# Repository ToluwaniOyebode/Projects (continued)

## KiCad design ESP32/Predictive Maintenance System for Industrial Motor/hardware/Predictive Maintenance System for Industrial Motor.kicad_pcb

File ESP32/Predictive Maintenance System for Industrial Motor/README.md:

# Predictive Maintenance System for Industrial Motor
Generated using KiCad Industrial Setup Script

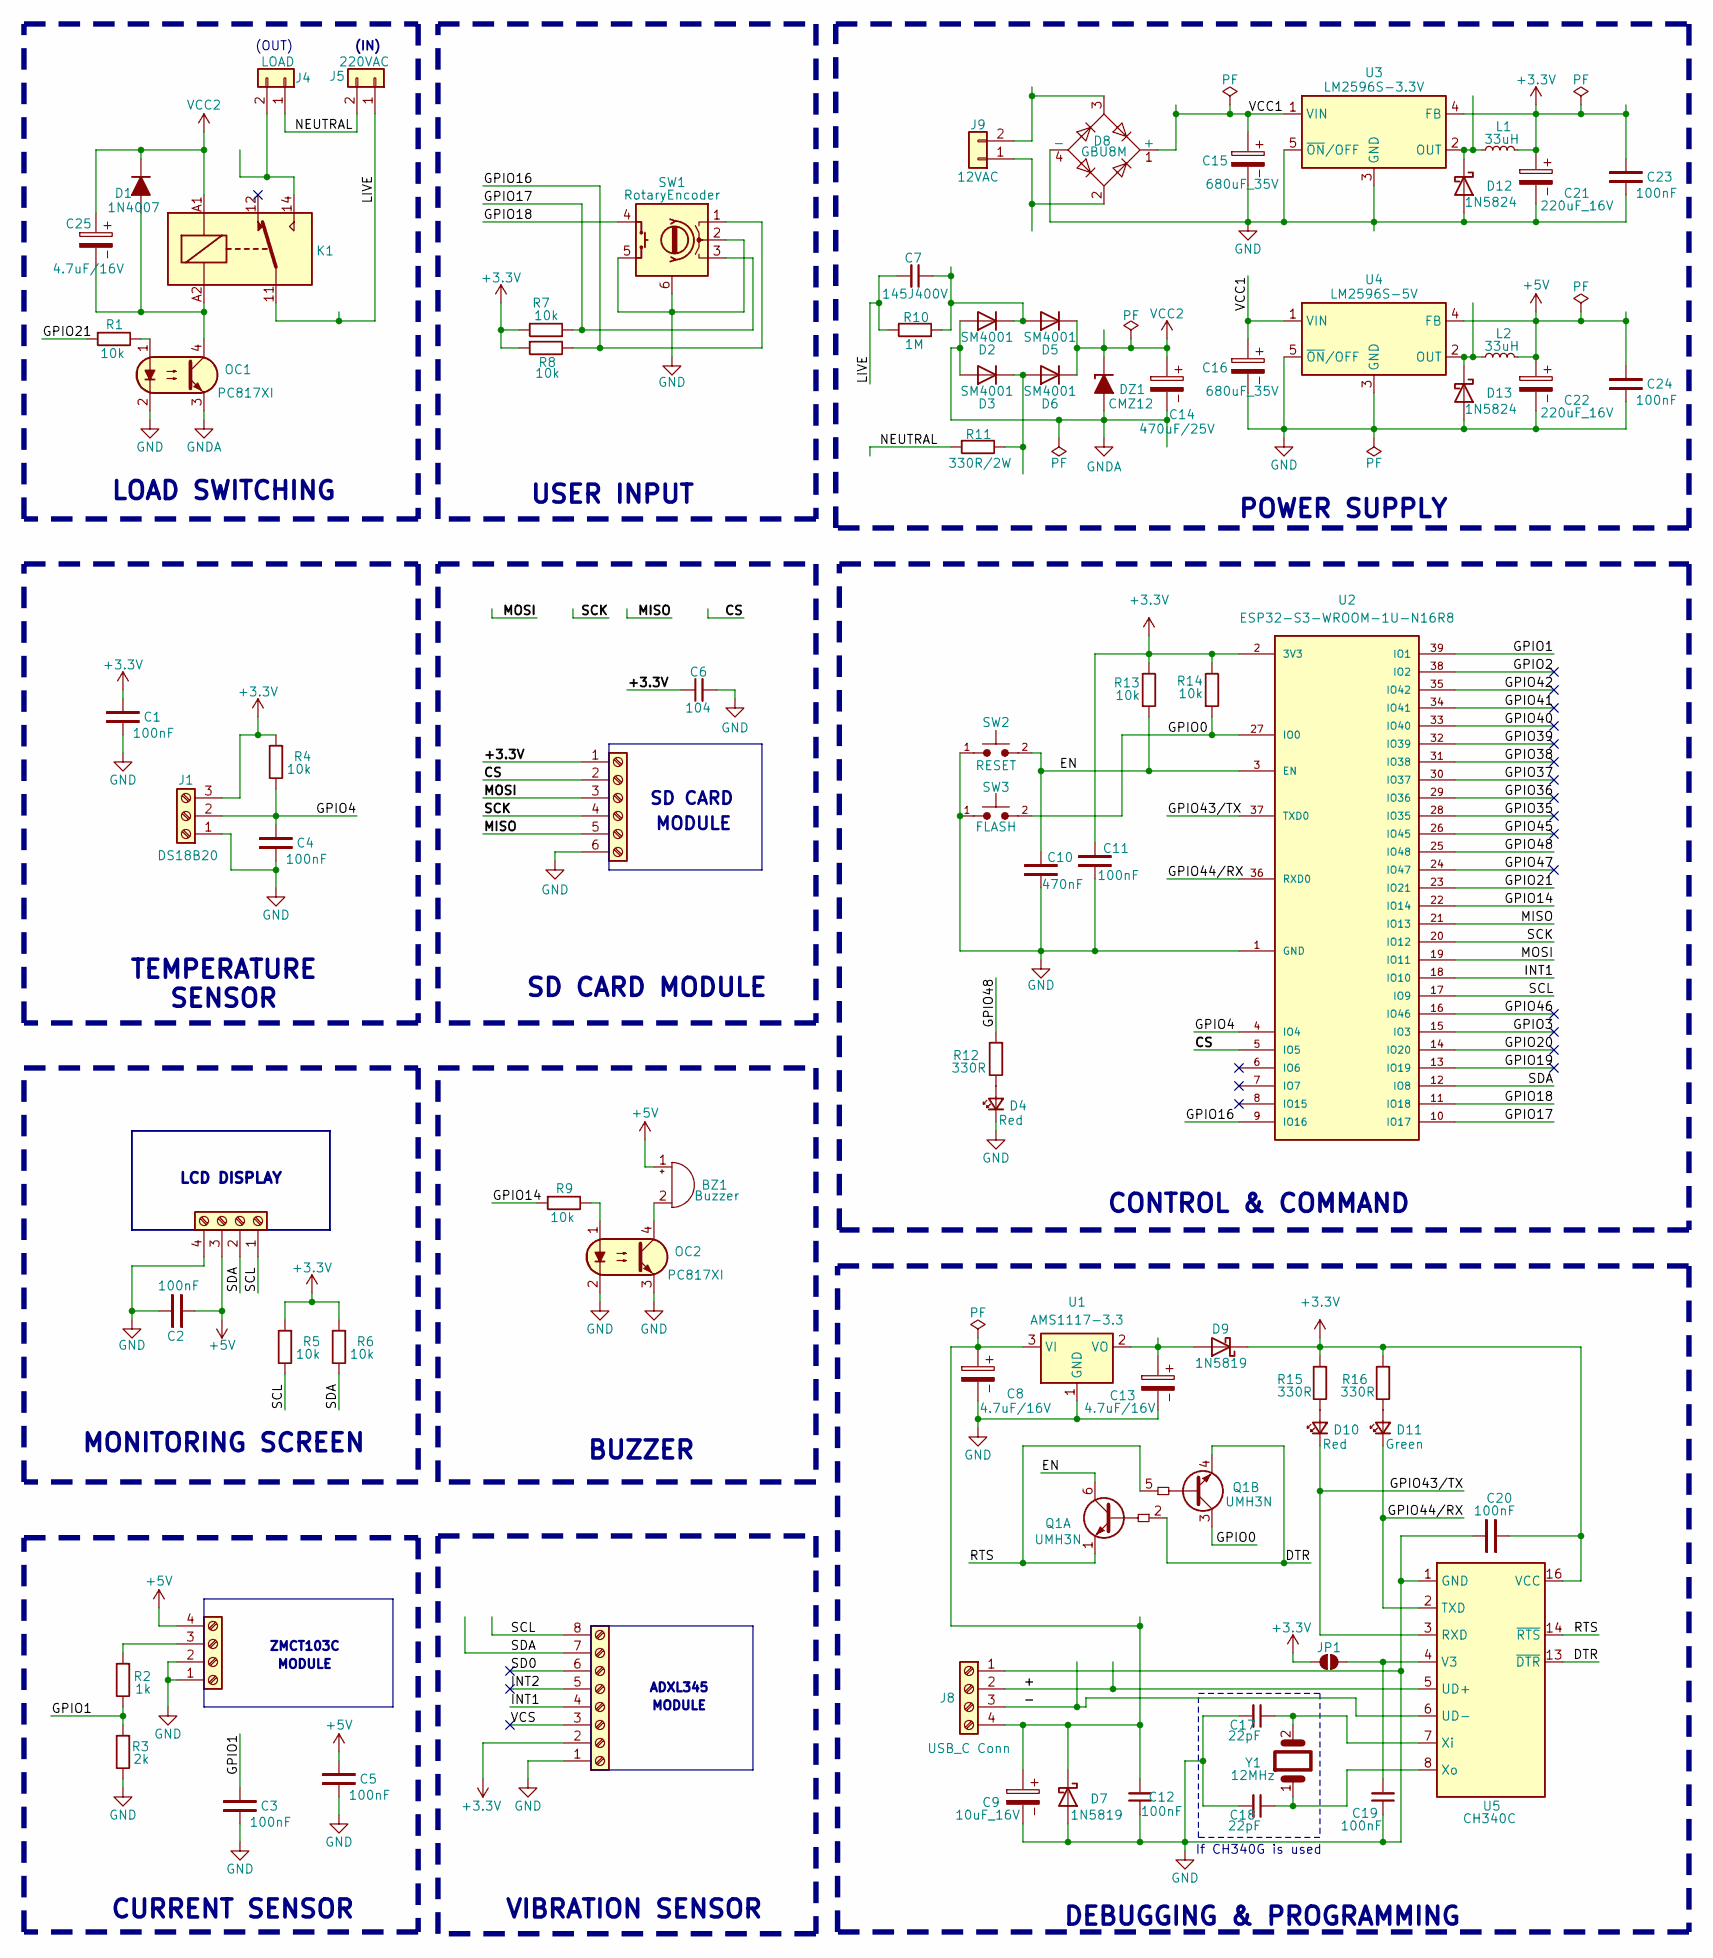
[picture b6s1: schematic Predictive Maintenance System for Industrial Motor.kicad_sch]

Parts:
BZ1: Buzzer; Buzzer_15x7.5RM7.6
C1, C2, C3, C4, C5, C11, C12, C19, C20, C23, C24: 100nF; C_0805_2012Metric_Pad1.18x1.45mm_HandSolder
C6: 104; C_0805_2012Metric
C7: 145J400V; C_Rect_L19.0mm_W6.0mm_P15.00mm_MKS4
C8, C13, C25: 4.7uF/16V; CP_EIA-3528-21_Kemet-B_HandSolder
C9: 10uF_16V; CP_Radial_D5.0mm_P2.00mm
C10: 470nF; C_0805_2012Metric_Pad1.18x1.45mm_HandSolder
C14: 470uF/25V; CP_Elec_8x11.9
C15, C16: 680uF_35V; CP_Elec_10x12.5
C17, C18: 22pF; C_0805_2012Metric_Pad1.18x1.45mm_HandSolder
C21, C22: 220uF_16V; CP_Elec_6.3x7.7
D1: 1N4007; D_SMA
D2, D3, D5, D6: SM4001; D_SMA
D4, D10: Red; LED_D3.0mm
D7, D9: 1N5819; D_SMA
D8: GBU8M; Diode_Bridge_Vishay_GBU
D11: Green; LED_D3.0mm
D12, D13: 1N5824; D_SMA
DZ1: CMZ12; D_SOD-123
J1: DS18B20; PinHeader_1x03_P2.54mm_Vertical
J2: CURRENT SENSOR; PinSocket_1x04_P2.54mm_Vertical
J3: OLED SCREEN; PinSocket_1x04_P2.54mm_Vertical
J4: LOAD; TerminalBlock_Phoenix_MKDS-1,5-2_1x02_P5.00mm_Horizontal
J5: 220VAC; TerminalBlock_Phoenix_MKDS-1,5-2_1x02_P5.00mm_Horizontal
J6: MPU6050; PinHeader_1x08_P2.54mm_Vertical
J7: SD MODULE; PinHeader_1x06_P2.54mm_Vertical
J8: USB_C Conn; PinHeader_1x04_P2.54mm_Vertical
J9: 12VAC; TerminalBlock_Phoenix_MKDS-1,5-2_1x02_P5.00mm_Horizontal
JP1: SolderJumper-2_P1.3mm_Open_Pad1.0x1.5mm
K1: FINDER-36.11; Relay_SPDT_Finder_36.11
L1, L2: 33uH; L_12x12mm_H6mm
OC1, OC2: PC817XI; DIP-4_W7.62mm_SMDSocket_SmallPads
Q1: UMH3N; SOT-363_SC-70-6
R1, R4, R5, R6, R7, R8, R9, R13, R14: 10k; R_0805_2012Metric
R2: 1k; R_0805_2012Metric
R3: 2k; R_0805_2012Metric
R10: 1M; R_Axial_DIN0207_L6.3mm_D2.5mm_P7.62mm_Horizontal
R11: 330R/2W; R_Axial_DIN0309_L9.0mm_D3.2mm_P20.32mm_Horizontal
R12, R15, R16: 330R; R_0805_2012Metric
SW1: RotaryEncoder; PinHeader_1x06_P2.54mm_Vertical
SW2: RESET; SW_SPST_CK_KXT3
SW3: FLASH; SW_SPST_CK_KXT3
U1: AMS1117-3.3; SOT-223-3_TabPin2
U2: ESP32-S3-WROOM-1U-N16R8; PARTREV v1.1
U3: LM2596S-3.3V; TO-263-5_TabPin6
U4: LM2596S-5V; TO-263-5_TabPin6
U5: CH340C; SOIC-16_3.9x9.9mm_P1.27mm
Y1: 12MHz; Crystal_HC49-4H_Vertical

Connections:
+3.3V: C1.2, C6.1, C11.2, C20.1, C21.1, C23.2, D9.1 (K), J1.3, J6.2, J7.1, JP1.2 (B), L1.2, R4.1, R5.1, R6.1, R7.2, R8.1, R13.2, R14.2, R15.1, R16.1, U2.2 (3V3), U3.4 (FB), U5.16 (VCC)
+5V: BZ1.1 (+), C2.1, C5.2, C22.1, C24.2, J2.4, J3.3, L2.2, U4.4 (FB)
/+: J8.2, U5.5 (UD+)
/-: J8.3, U5.6 (UD-)
/CS: J7.2, U2.5 (IO5)
/DTR: Q1.2 (B1), Q1.4 (E2), U5.13 (~DTR)
/EN: C10.2, Q1.6 (C1), R13.1, SW2.2, U2.3 (EN)
/GPIO0: Q1.3 (C2), R14.1, SW3.2, U2.27 (IO0)
/GPIO1: C3.2, R2.2, R3.1, U2.39 (IO1)
/GPIO2: U2.38 (IO2)
/GPIO3: U2.15 (IO3)
/GPIO4: C4.2, J1.2, R4.2, U2.4 (IO4)
/GPIO14: R9.1, U2.22 (IO14)
/GPIO16: R8.2, SW1.1 (A), U2.9 (IO16)
/GPIO17: R7.1, SW1.3 (B), U2.10 (IO17)
/GPIO18: SW1.4 (S1), U2.11 (IO18)
/GPIO19: U2.13 (IO19)
/GPIO20: U2.14 (IO20)
/GPIO21: R1.1, U2.23 (IO21)
/GPIO35: U2.28 (IO35)
/GPIO36: U2.29 (IO36)
/GPIO37: U2.30 (IO37)
/GPIO38: U2.31 (IO38)
/GPIO39: U2.32 (IO39)
/GPIO40: U2.33 (IO40)
/GPIO41: U2.34 (IO41)
/GPIO42: U2.35 (IO42)
/GPIO43/TX: D10.1 (K), U2.37 (TXD0), U5.3 (RXD)
/GPIO44/RX: D11.1 (K), U2.36 (RXD0), U5.2 (TXD)
/GPIO45: U2.26 (IO45)
/GPIO46: U2.16 (IO46)
/GPIO47: U2.24 (IO47)
/GPIO48: R12.1, U2.25 (IO48)
/INT1: J6.4, U2.18 (IO10)
/INT2: J6.5
/LIVE: C7.2, J5.1, K1.11, R10.2
/MISO: J7.5, U2.21 (IO13)
/MOSI: J7.3, U2.19 (IO11)
/NEUTRAL: J4.1, J5.2, R11.1
/RTS: Q1.1 (E1), Q1.5 (B2), U5.14 (~RTS)
/SCK: J7.4, U2.20 (IO12)
/SCL: J3.1, J6.8, R5.2, U2.17 (IO9)
/SD0: J6.6
/SDA: J3.2, J6.7, R6.2, U2.12 (IO8)
/VCC1: C15.1, C16.1, D8.1 (+), U3.1 (VIN), U4.1 (VIN)
/VCS: J6.3
GND: C1.1, C2.2, C3.1, C4.1, C5.1, C6.2, C8.2, C9.2, C10.1, C11.1, C12.1, C13.2, C15.2, C16.2, C17.2, C18.2, C19.1, C20.2, C21.2, C22.2, C23.1, C24.1, D4.1 (K), D7.2 (A), D8.4 (-), D12.2 (A), D13.2 (A), J1.1, J2.1, J2.2, J3.4, J6.1, J7.6, J8.1, OC1.2, OC2.2, OC2.3, R3.2, SW1.2 (C), SW1.5 (S2), SW1.6 (MP), SW2.1, SW3.1, U1.1 (GND), U2.1 (GND), U2.40 (GND), U2.41 (GND), U3.3 (GND), U3.5 (~ON/OFF), U3.6 (GND), U4.3 (GND), U4.5 (~ON/OFF), U4.6 (GND), U5.1 (GND)
GNDA: C14.2, D2.2 (A), D3.2 (A), DZ1.2 (A), OC1.3
unnamed: BZ1.2 (-), OC2.4
unnamed: C25.2, D1.2 (A), K1.A2, OC1.4
unnamed: C7.1, D2.1 (K), D5.2 (A), R10.1
unnamed: D3.1 (K), D6.2 (A), R11.2
unnamed: D4.2 (A), R12.2
unnamed: C8.1, C9.1, C12.2, D7.1 (K), J8.4, U1.3 (VI)
unnamed: C13.1, D9.2 (A), U1.2 (VO)
unnamed: D10.2 (A), R15.2
unnamed: D11.2 (A), R16.2
unnamed: D12.1 (K), L1.1, U3.2 (OUT)
unnamed: D13.1 (K), L2.1, U4.2 (OUT)
unnamed: J2.3, R2.1
unnamed: J4.2, K1.14
unnamed: D8.2, J9.1
unnamed: D8.3, J9.2
unnamed: C19.2, JP1.1 (A), U5.4 (V3)
unnamed: OC1.1, R1.2
unnamed: OC2.1, R9.2
unnamed: C17.1, U5.7 (Xi), Y1.2
unnamed: C18.1, U5.8 (Xo), Y1.1
VCC2: C14.1, C25.1, D1.1 (K), D5.1 (K), D6.1 (K), DZ1.1 (K), K1.A1

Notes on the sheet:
VIBRATION SENSOR
DEBUGGING & PROGRAMMING
LOAD SWITCHING
CURRENT SENSOR
ADXL345
TEMPERATURE SENSOR
MODULE
(IN)
LCD DISPLAY
ZMCT103C
BUZZER
SD CARD
MONITORING SCREEN
If CH340G is used
USER INPUT
POWER SUPPLY
CONTROL & COMMAND
(OUT)
SD CARD MODULE

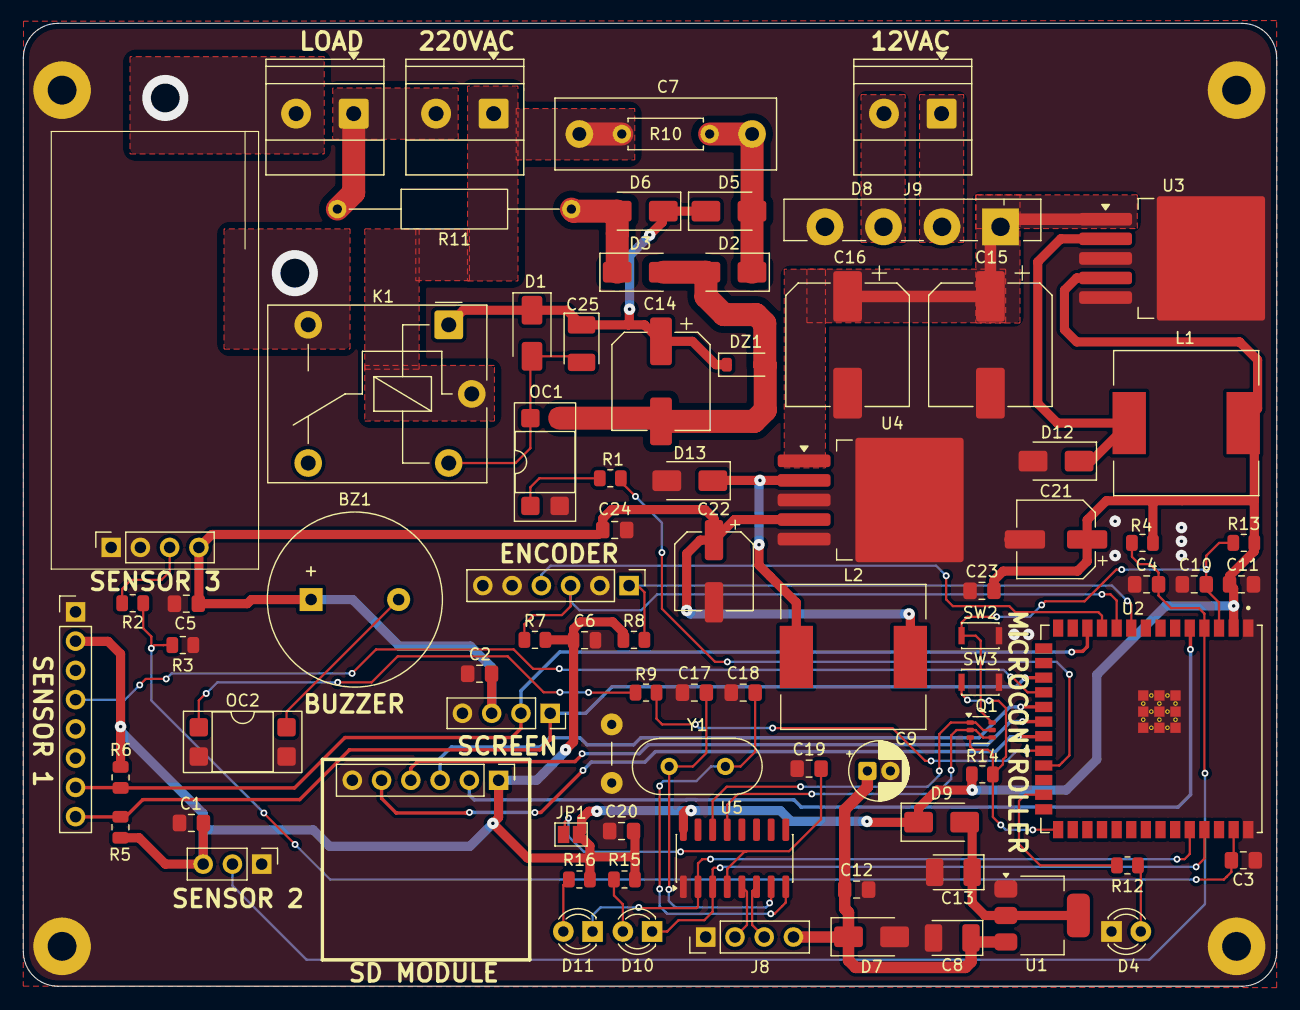
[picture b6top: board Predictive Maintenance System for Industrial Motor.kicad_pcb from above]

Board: 2 copper layers, 108.8 x 83.6 mm, 81 parts (0 on the bottom side), 51 nets.

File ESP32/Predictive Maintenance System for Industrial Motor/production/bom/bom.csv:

Designator,Footprint,Quantity,Value,LCSC Part #
BZ1,Buzzer_15x7.5RM7.6,1,Buzzer,
"C1, C11, C12, C19, C2, C20, C23, C24, C3, C4, C5",0805,11,100nF,
C10,0805,1,470nF,
"C13, C25, C8",CP_EIA-3528-21_Kemet-B_HandSolder,3,4.7uF/16V,
C14,CP_Elec_8x11.9,1,470uF/25V,
"C15, C16",CP_Elec_10x12.5,2,680uF_35V,
"C17, C18",0805,2,22pF,
"C21, C22",CP_Elec_6.3x7.7,2,220uF_16V,
C6,0805,1,104,
C7,C_Rect_L19.0mm_W6.0mm_P15.00mm_MKS4,1,145J400V,
C9,CP_Radial_D5.0mm_P2.00mm,1,10uF_16V,
D1,D_SMA,1,1N4007,
"D10, D4",LED_D3.0mm,2,Red,
D11,LED_D3.0mm,1,Green,
"D12, D13",D_SMA,2,1N5824,
"D2, D3, D5, D6",D_SMA,4,SM4001,
"D7, D9",D_SMA,2,1N5819,
D8,Diode_Bridge_Vishay_GBU,1,GBU8M,
DZ1,D_SOD-123,1,CMZ12,
J1,PinHeader_1x03_P2.54mm_Vertical,1,DS18B20,
J2,PinSocket_1x04_P2.54mm_Vertical,1,CURRENT SENSOR,
J3,PinSocket_1x04_P2.54mm_Vertical,1,OLED SCREEN,
J4,"TerminalBlock_Phoenix_MKDS-1,5-2_1x02_P5.00mm_Horizontal",1,LOAD,
J5,"TerminalBlock_Phoenix_MKDS-1,5-2_1x02_P5.00mm_Horizontal",1,220VAC,
J6,PinHeader_1x08_P2.54mm_Vertical,1,MPU6050,
J7,PinHeader_1x06_P2.54mm_Vertical,1,SD MODULE,
J8,PinHeader_1x04_P2.54mm_Vertical,1,USB_C Conn,
J9,"TerminalBlock_Phoenix_MKDS-1,5-2_1x02_P5.00mm_Horizontal",1,12VAC,
JP1,SolderJumper-2_P1.3mm_Open_Pad1.0x1.5mm,1,~,
K1,Relay_SPDT_Finder_36.11,1,FINDER-36.11,
"L1, L2",L_12x12mm_H6mm,2,33uH,
"OC1, OC2",DIP-4_W7.62mm_SMDSocket_SmallPads,2,PC817XI,
Q1,SOT-363_SC-70-6,1,UMH3N,
"R1, R13, R14, R4, R5, R6, R7, R8, R9",0805,9,10k,
R10,R_Axial_DIN0207_L6.3mm_D2.5mm_P7.62mm_Horizontal,1,1M,
R11,R_Axial_DIN0309_L9.0mm_D3.2mm_P20.32mm_Horizontal,1,330R/2W,
"R12, R15, R16",0805,3,330R,
R2,0805,1,1k,
R3,0805,1,2k,
SW1,PinHeader_1x06_P2.54mm_Vertical,1,RotaryEncoder,
SW2,SW_SPST_CK_KXT3,1,RESET,
SW3,SW_SPST_CK_KXT3,1,FLASH,
U1,SOT-223-3_TabPin2,1,AMS1117-3.3,
U2,ESP32-S3-WROOM-1U-N16R8,1,ESP32-S3-WROOM-1U-N16R8,
U3,TO-263-5_TabPin6,1,LM2596S-3.3V,
U4,TO-263-5_TabPin6,1,LM2596S-5V,
U5,SOIC-16_3.9x9.9mm_P1.27mm,1,CH340C,
Y1,Crystal_HC49-4H_Vertical,1,12MHz,

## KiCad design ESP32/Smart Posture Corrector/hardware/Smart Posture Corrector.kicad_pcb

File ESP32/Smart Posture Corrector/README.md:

# Smart Posture Corrector
Generated using KiCad Industrial Setup Script

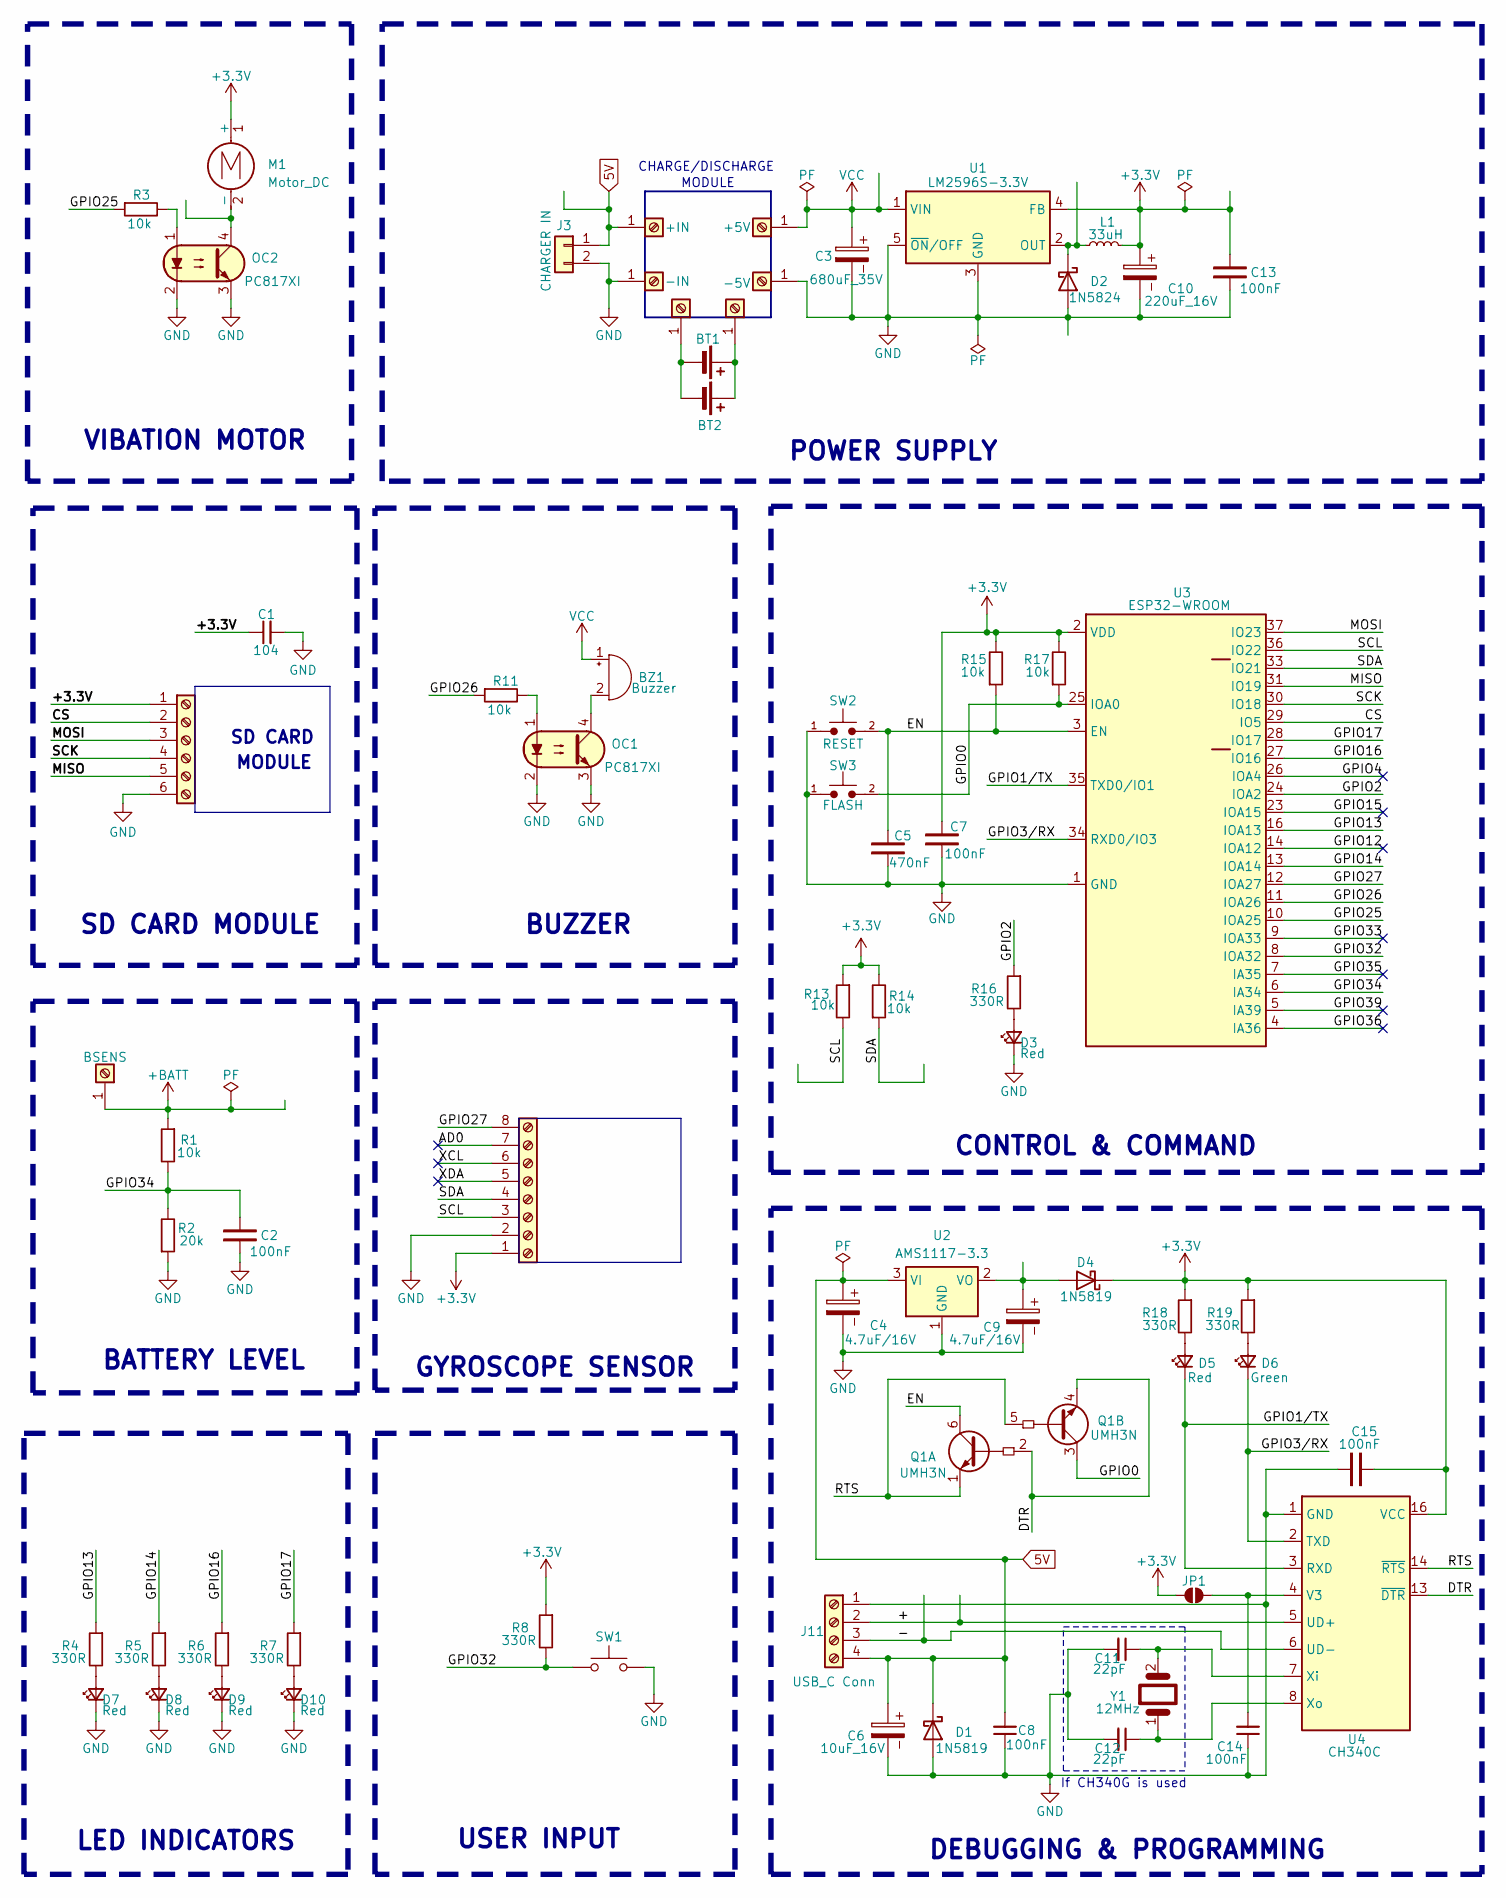
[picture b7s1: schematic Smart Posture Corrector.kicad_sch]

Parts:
BT1, BT2: Battery_Cell
BZ1: Buzzer; Buzzer_15x7.5RM7.6
C1: 104; C_0805_2012Metric
C2, C7, C8, C13, C14, C15: 100nF; C_0805_2012Metric_Pad1.18x1.45mm_HandSolder
C3: 680uF_35V; CP_Elec_10x12.5
C4, C9: 4.7uF/16V; CP_EIA-3528-21_Kemet-B_HandSolder
C5: 470nF; C_0805_2012Metric_Pad1.18x1.45mm_HandSolder
C6: 10uF_16V; CP_Radial_D5.0mm_P2.00mm
C10: 220uF_16V; CP_Elec_6.3x7.7
C11, C12: 22pF; C_0805_2012Metric_Pad1.18x1.45mm_HandSolder
D1, D4: 1N5819; D_SMA
D2: 1N5824; D_SMA
D3, D5, D7, D8, D9, D10: Red; LED_D3.0mm
D6: Green; LED_D3.0mm
J1: MPU6050; PinHeader_1x08_P2.54mm_Vertical
J3: CHARGER IN
J5: +IN; TestPoint_Keystone_5015_Micro_Mini
J6: -IN; TestPoint_Keystone_5015_Micro_Mini
J7: -BATT
J8: +BATT
J9: +5V; TestPoint_Keystone_5015_Micro_Mini
J10: -5V; TestPoint_Keystone_5015_Micro_Mini
J11: USB_C Conn; PinHeader_1x04_P2.54mm_Vertical
J15: SD MODULE; PinHeader_1x06_P2.54mm_Vertical
J24: BSENS; SolderWire-0.1sqmm_1x01_D0.4mm_OD1mm
JP1: SolderJumper-2_P1.3mm_Open_Pad1.0x1.5mm
L1: 33uH; L_12x12mm_H6mm
M1: Motor_DC; PinHeader_1x02_P2.54mm_Vertical
OC1, OC2: PC817XI; SMDIP-4_W9.53mm
Q1: UMH3N; SOT-363_SC-70-6
R1, R3, R11, R13, R14, R15, R17: 10k; R_0805_2012Metric
R2: 20k; R_0805_2012Metric
R4, R5, R6, R7, R8, R16, R18, R19: 330R; R_0805_2012Metric
SW1: SW_Push; SW_PUSH_6mm_H13mm
SW2: RESET; SW_SPST_CK_KXT3
SW3: FLASH; SW_SPST_CK_KXT3
U1: LM2596S-3.3V; TO-263-5_TabPin6
U2: AMS1117-3.3; SOT-223-3_TabPin2
U3: ESP32-WROOM; ESP32-WROOM-32
U4: CH340C; SOIC-16_3.9x9.9mm_P1.27mm
Y1: 12MHz; Crystal_HC49-4H_Vertical

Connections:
5V: C4.1, C6.1, C8.2, D1.1 (K), J3.1, J5.1, J11.4, U2.3 (VI)
+3.3V: C1.1, C7.2, C10.1, C13.2, C15.1, D4.1 (K), J1.1, J15.1, JP1.2 (B), L1.2, M1.1 (+), R8.1, R13.1, R14.2, R15.2, R17.2, R18.1, R19.1, U1.4 (FB), U3.2 (VDD), U4.16 (VCC)
+BATT: J24.1, R1.1
/+: J11.2, U4.5 (UD+)
/-: J11.3, U4.6 (UD-)
/AD0: J1.7
/CS: J15.2, U3.29 (IO5)
/DTR: Q1.2 (B1), Q1.4 (E2), U4.13 (~DTR)
/EN: C5.2, Q1.6 (C1), R15.1, SW2.2, U3.3 (EN)
/GPIO0: Q1.3 (C2), R17.1, SW3.2, U3.25 (IOA0)
/GPIO1/TX: D5.1 (K), U3.35 (TXD0/IO1), U4.3 (RXD)
/GPIO2: R16.1, U3.24 (IOA2)
/GPIO3/RX: D6.1 (K), U3.34 (RXD0/IO3), U4.2 (TXD)
/GPIO4: U3.26 (IOA4)
/GPIO12: U3.14 (IOA12)
/GPIO13: R4.1, U3.16 (IOA13)
/GPIO14: R5.1, U3.13 (IOA14)
/GPIO15: U3.23 (IOA15)
/GPIO16: R6.1, U3.27 (IO16)
/GPIO17: R7.1, U3.28 (IO17)
/GPIO25: R3.1, U3.10 (IOA25)
/GPIO26: R11.1, U3.11 (IOA26)
/GPIO27: J1.8, U3.12 (IOA27)
/GPIO32: R8.2, SW1.1, U3.8 (IOA32)
/GPIO33: U3.9 (IOA33)
/GPIO34: C2.2, R1.2, R2.2, U3.6 (IA34)
/GPIO35: U3.7 (IA35)
/GPIO36: U3.4 (IA36)
/GPIO39: U3.5 (IA39)
/MISO: J15.5, U3.31 (IO19)
/MOSI: J15.3, U3.37 (IO23)
/RTS: Q1.1 (E1), Q1.5 (B2), U4.14 (~RTS)
/SCK: J15.4, U3.30 (IO18)
/SCL: J1.3, R13.2, U3.36 (IO22)
/SDA: J1.4, R14.1, U3.33 (IO21)
/XCL: J1.6
/XDA: J1.5
GND: C1.2, C2.1, C3.2, C4.2, C5.1, C6.2, C7.1, C8.1, C9.2, C10.2, C11.2, C12.2, C13.1, C14.1, C15.2, D1.2 (A), D2.2 (A), D3.1 (K), D7.1 (K), D8.1 (K), D9.1 (K), D10.1 (K), J1.2, J3.2, J6.1, J10.1, J11.1, J15.6, OC1.2, OC1.3, OC2.2, OC2.3, R2.1, SW1.2, SW2.1, SW3.1, U1.3 (GND), U1.5 (~ON/OFF), U1.6 (GND), U2.1 (GND), U3.1 (GND), U3.15 (GND), U3.38 (GND), U3.39 (GND), U4.1 (GND); also elsewhere on the board
unnamed: BT1.1 (+), BT2.1 (+), J8.1
unnamed: BT1.2 (-), BT2.2 (-), J7.1
unnamed: BZ1.2 (-), OC1.4
unnamed: D2.1 (K), L1.1, U1.2 (OUT)
unnamed: D3.2 (A), R16.2
unnamed: C9.1, D4.2 (A), U2.2 (VO)
unnamed: D5.2 (A), R18.2
unnamed: D6.2 (A), R19.2
unnamed: D7.2 (A), R4.2
unnamed: D8.2 (A), R5.2
unnamed: D9.2 (A), R6.2
unnamed: D10.2 (A), R7.2
unnamed: C14.2, JP1.1 (A), U4.4 (V3)
unnamed: M1.2 (-), OC2.4
unnamed: OC1.1, R11.2
unnamed: OC2.1, R3.2
unnamed: C11.1, U4.7 (Xi), Y1.2
unnamed: C12.1, U4.8 (Xo), Y1.1
VCC: BZ1.1 (+), C3.1, J9.1, U1.1 (VIN)

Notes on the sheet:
GYROSCOPE SENSOR
BUZZER
MODULE
BATTERY LEVEL
VIBATION MOTOR
LED INDICATORS
SD CARD
If CH340G is used
CONTROL & COMMAND
SD CARD MODULE
USER INPUT
DEBUGGING & PROGRAMMING
POWER SUPPLY
CHARGE/DISCHARGE

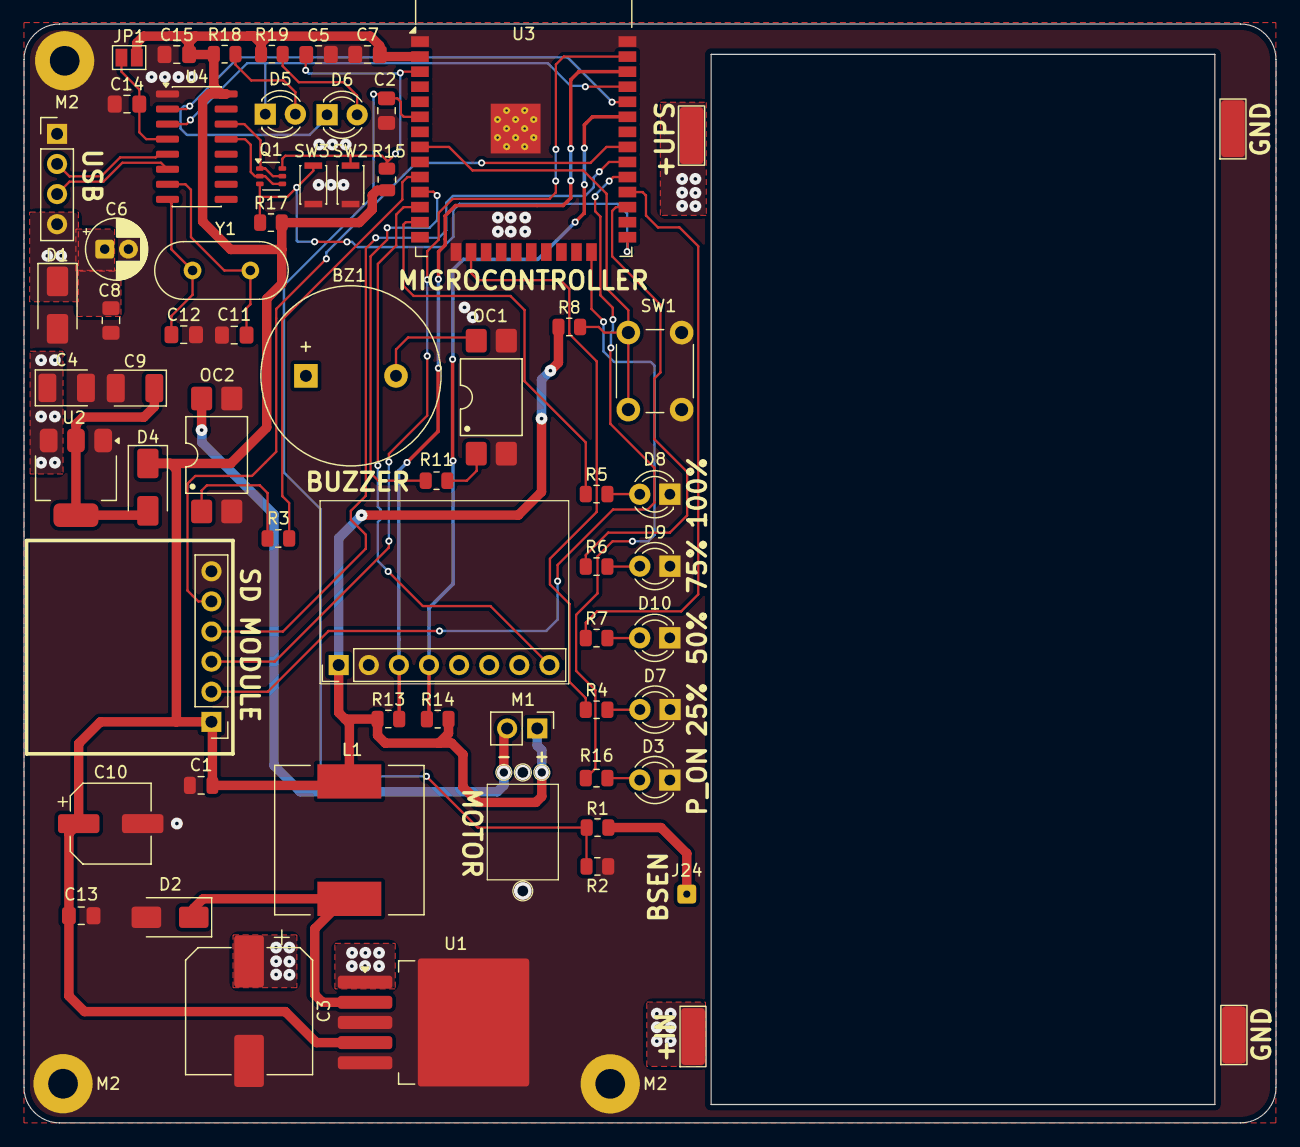
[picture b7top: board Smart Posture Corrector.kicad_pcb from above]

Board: 2 copper layers, 105.6 x 92.7 mm, 67 parts (0 on the bottom side), 45 nets.

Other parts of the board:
M2, M2#2, M2#3: MountingHole_2.5mm_Pad

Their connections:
GND: M2.1, M2#2.1, M2#3.1; also elsewhere on the board

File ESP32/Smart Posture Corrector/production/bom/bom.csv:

Designator,Footprint,Quantity,Value,LCSC Part #
BZ1,Buzzer_15x7.5RM7.6,1,Buzzer,
C1,0805,1,104,
C10,CP_Elec_6.3x7.7,1,220uF_16V,
"C11, C12",0805,2,22pF,
"C13, C14, C15, C2, C7, C8",0805,6,100nF,
C3,CP_Elec_10x12.5,1,680uF_35V,
"C4, C9",CP_EIA-3528-21_Kemet-B_HandSolder,2,4.7uF/16V,
C5,0805,1,470nF,
C6,CP_Radial_D5.0mm_P2.00mm,1,10uF_16V,
"D1, D4",D_SMA,2,1N5819,
"D10, D3, D5, D7, D8, D9",LED_D3.0mm,6,Red,
D2,D_SMA,1,1N5824,
D6,LED_D3.0mm,1,Green,
J1,PinHeader_1x08_P2.54mm_Vertical,1,MPU6050,
J10,TestPoint_Keystone_5015_Micro_Mini,1,-5V,
J11,PinHeader_1x04_P2.54mm_Vertical,1,USB_C Conn,
J15,PinHeader_1x06_P2.54mm_Vertical,1,SD MODULE,
J24,SolderWire-0.1sqmm_1x01_D0.4mm_OD1mm,1,BSENS,
J5,TestPoint_Keystone_5015_Micro_Mini,1,+IN,
J6,TestPoint_Keystone_5015_Micro_Mini,1,-IN,
J9,TestPoint_Keystone_5015_Micro_Mini,1,+5V,
JP1,SolderJumper-2_P1.3mm_Open_Pad1.0x1.5mm,1,~,
L1,L_12x12mm_H6mm,1,33uH,
M1,PinHeader_1x02_P2.54mm_Vertical,1,Motor_DC,
"OC1, OC2",SMDIP-4_W9.53mm,2,PC817XI,
Q1,SOT-363_SC-70-6,1,UMH3N,
"R1, R11, R13, R14, R15, R17, R3",0805,7,10k,
"R16, R18, R19, R4, R5, R6, R7, R8",0805,8,330R,
R2,0805,1,20k,
SW1,SW_PUSH_6mm_H13mm,1,SW_Push,
SW2,SW_SPST_CK_KXT3,1,RESET,
SW3,SW_SPST_CK_KXT3,1,FLASH,
U1,TO-263-5_TabPin6,1,LM2596S-3.3V,
U2,SOT-223-3_TabPin2,1,AMS1117-3.3,
U3,ESP32-WROOM-32,1,ESP32-WROOM,
U4,SOIC-16_3.9x9.9mm_P1.27mm,1,CH340C,
Y1,Crystal_HC49-4H_Vertical,1,12MHz,

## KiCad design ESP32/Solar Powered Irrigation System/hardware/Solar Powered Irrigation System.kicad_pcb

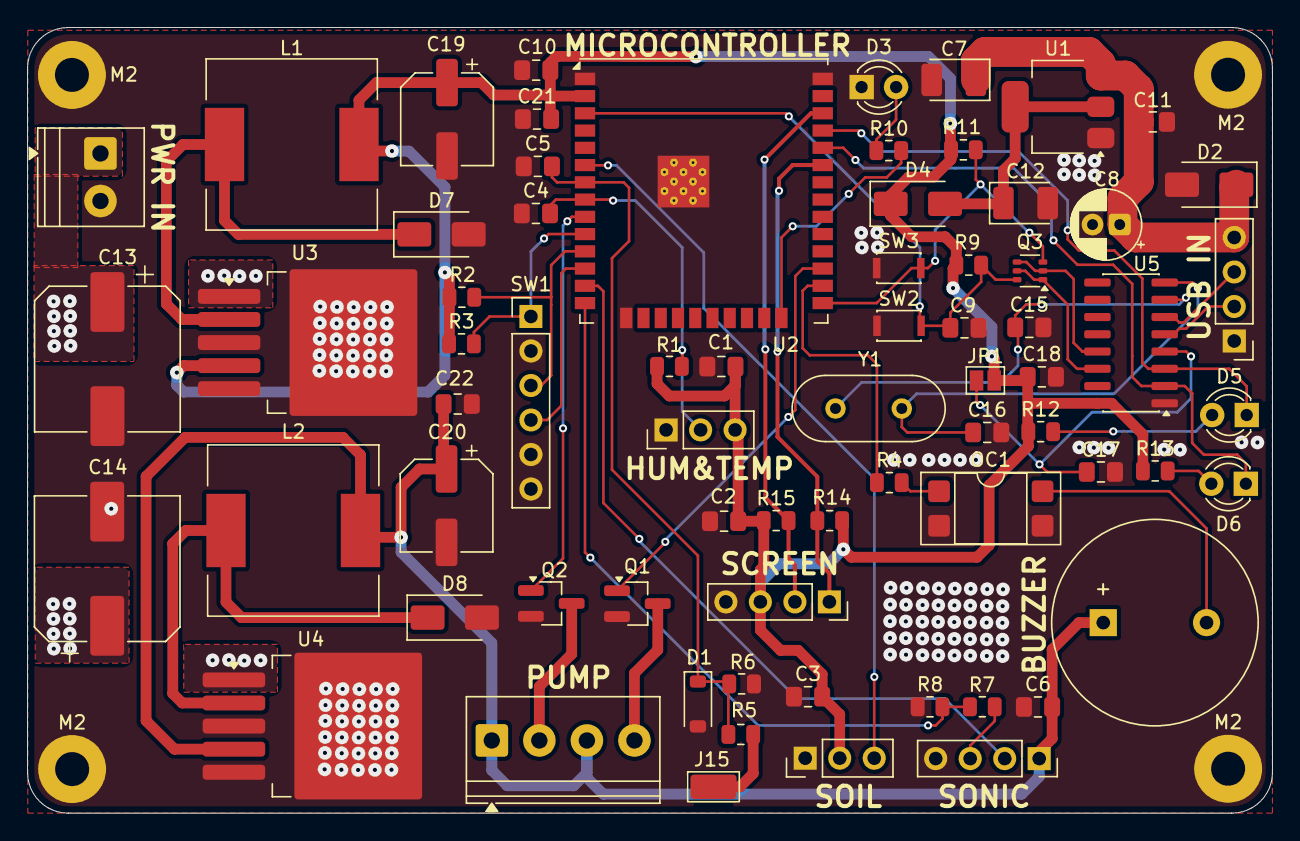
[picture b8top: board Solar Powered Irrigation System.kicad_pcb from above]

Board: 2 copper layers, 91.6 x 57.8 mm, 74 parts (0 on the bottom side), 42 nets.

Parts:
BZ1: Buzzer; Buzzer_15x7.5RM7.6
C1, C2, C3, C4, C5, C6, C10, C11, C17, C18, C21, C22: 100nF; C_0805_2012Metric_Pad1.18x1.45mm_HandSolder
C7, C12: 4.7uF/16V; CP_EIA-3528-21_Kemet-B_HandSolder
C8: 10uF_16V; CP_Radial_D5.0mm_P2.00mm
C9: 470nF; C_0805_2012Metric_Pad1.18x1.45mm_HandSolder
C13, C14: 680uF_35V; CP_Elec_10x12.5
C15, C16: 22pF; C_0805_2012Metric_Pad1.18x1.45mm_HandSolder
C19, C20: 220uF_16V; CP_Elec_6.3x7.7
D1: 3.3V; D_SOD-123
D2, D4: 1N5819; D_SMA
D3, D5: Red; LED_D3.0mm
D6: Green; LED_D3.0mm
D7, D8: 1N5824; D_SMA
J1: PUMP; TerminalBlock_Phoenix_PT-1,5-4-3.5-H_1x04_P3.50mm_Horizontal
J2: SOIL SENSOR; PinHeader_1x03_P2.54mm_Vertical
J3: AM2301A; PinHeader_1x03_P2.54mm_Vertical
J4: OLED SCREEN; PinSocket_1x04_P2.54mm_Vertical
J5: Ultra Sonic; PinSocket_1x04_P2.54mm_Vertical
J7: USB_C Conn; PinHeader_1x04_P2.54mm_Vertical
J11: INPUT; TerminalBlock_Phoenix_PT-1,5-2-3.5-H_1x02_P3.50mm_Horizontal
J15: BSEN; TestPoint_Keystone_5015_Micro_Mini
JP1: SolderJumper-2_P1.3mm_Open_Pad1.0x1.5mm
L1, L2: 33uH; L_12x12mm_H6mm
M2, M2#2, M2#3, M2#4: MountingHole_2.5mm_Pad
OC1: PC817XI; DIP-4_W7.62mm_SMDSocket_SmallPads
Q1, Q2: IRLML6344; SOT-23_Handsoldering
Q3: UMH3N; SOT-363_SC-70-6
R1, R2, R3, R4, R5, R9, R11, R14, R15: 10k; R_0805_2012Metric
R6: 20k; R_0805_2012Metric
R7: 1k; R_0805_2012Metric
R8: 2k; R_0805_2012Metric
R10, R12, R13: 330R; R_0805_2012Metric
SW1: RotaryEncoder; PinHeader_1x06_P2.54mm_Vertical
SW2: RESET; SW_SPST_CK_KXT3
SW3: FLASH; SW_SPST_CK_KXT3
U1: AMS1117-3.3; SOT-223-3_TabPin2
U2: ESP32-WROOM; ESP32-WROOM-32U
U3, U4: LM2596S-3.3V; TO-263-5_TabPin6
U5: CH340C; SOIC-16_3.9x9.9mm_P1.27mm
Y1: 12MHz; Crystal_HC49-4H_Vertical

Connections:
+3.3V: C1.2, C2.1, C3.2, C10.2, C18.1, C19.1, C21.2, D4.1 (K), J2.2, J3.3, J4.3, JP1.2 (B), L1.2, R1.1, R2.2, R3.1, R9.2, R11.2, R12.1, R13.1, R14.1, R15.1, U2.2 (VDD), U3.4 (FB), U5.16 (VCC)
+5V: BZ1.1 (+), C6.2, C20.1, C22.2, J1.1, J1.3, J5.1, L2.2, U4.4 (FB)
+BATT: J15.1, R5.1
/+: J7.2, U5.5 (UD+)
/-: J7.3, U5.6 (UD-)
/DTR: Q3.2 (B1), Q3.4 (E2), U5.13 (~DTR)
/EN: C9.2, Q3.6 (C1), R9.1, SW2.2, U2.3 (EN)
/GPIO0: Q3.3 (C2), R11.1, SW3.2, U2.25 (IOA0)
/GPIO1/TX: D5.1 (K), U2.35 (TXD0/IO1), U5.3 (RXD)
/GPIO2: R10.1, U2.24 (IOA2)
/GPIO3/RX: D6.1 (K), U2.34 (RXD0/IO3), U5.2 (TXD)
/GPIO4: R4.1, U2.26 (IOA4)
/GPIO12: R7.2, R8.2, U2.14 (IOA12)
/GPIO14: J5.2, U2.13 (IOA14)
/GPIO16: Q1.1 (G), U2.27 (IO16)
/GPIO25: R3.2, SW1.1 (A), U2.10 (IOA25)
/GPIO26: R2.1, SW1.3 (B), U2.11 (IOA26)
/GPIO27: SW1.4 (S1), U2.12 (IOA27)
/GPIO32: C4.2, J3.2, R1.2, U2.8 (IOA32)
/GPIO33: Q2.1 (G), U2.9 (IOA33)
/GPIO34: J2.3, U2.6 (IA34)
/GPIO35: C5.2, D1.1 (K), R5.2, R6.2, U2.7 (IA35)
/RTS: Q3.1 (E1), Q3.5 (B2), U5.14 (~RTS)
/SCL: J4.2, R15.2, U2.36 (IO22)
/SDA: J4.1, R14.2, U2.33 (IO21)
/VCC: C13.1, C14.1, J11.1, U3.1 (VIN), U4.1 (VIN)
GND: C1.1, C2.2, C3.1, C4.1, C5.1, C6.1, C7.2, C8.2, C9.1, C10.1, C11.1, C12.2, C13.2, C14.2, C15.2, C16.2, C17.1, C18.2, C19.2, C20.2, C21.1, C22.1, D1.2 (A), D2.2 (A), D3.1 (K), D7.2 (A), D8.2 (A), J2.1, J3.1, J4.4, J5.4, J7.1, J11.2, M2.1, M2#2.1, M2#3.1, M2#4.1, OC1.2, OC1.3, Q1.2 (S), Q2.2 (S), R6.1, R8.1, SW1.2 (C), SW1.5 (S2), SW1.6 (MP), SW2.1, SW3.1, U1.1 (GND), U2.1 (GND), U2.15 (GND), U2.38 (GND), U2.39 (GND), U3.3 (GND), U3.5 (~ON/OFF), U3.6 (GND), U4.3 (GND), U4.5 (~ON/OFF), U4.6 (GND), U5.1 (GND)
unnamed: BZ1.2 (-), OC1.4
unnamed: C7.1, C8.1, C11.2, D2.1 (K), J7.4, U1.3 (VI)
unnamed: D3.2 (A), R10.2
unnamed: C12.1, D4.2 (A), U1.2 (VO)
unnamed: D5.2 (A), R12.2
unnamed: D6.2 (A), R13.2
unnamed: D7.1 (K), L1.1, U3.2 (OUT)
unnamed: D8.1 (K), L2.1, U4.2 (OUT)
unnamed: J1.2, Q2.3 (D)
unnamed: J1.4, Q1.3 (D)
unnamed: J5.3, R7.1
unnamed: C17.2, JP1.1 (A), U5.4 (V3)
unnamed: OC1.1, R4.2
unnamed: C15.1, U5.7 (Xi), Y1.2
unnamed: C16.1, U5.8 (Xo), Y1.1

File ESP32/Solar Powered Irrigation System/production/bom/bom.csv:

Designator,Footprint,Quantity,Value,LCSC Part #
BZ1,Buzzer_15x7.5RM7.6,1,Buzzer,
"C1, C10, C11, C17, C18, C2, C21, C22, C3, C4, C5, C6",0805,12,100nF,
"C12, C7",CP_EIA-3528-21_Kemet-B_HandSolder,2,4.7uF/16V,
"C13, C14",CP_Elec_10x12.5,2,680uF_35V,
"C15, C16",0805,2,22pF,
"C19, C20",CP_Elec_6.3x7.7,2,220uF_16V,
C8,CP_Radial_D5.0mm_P2.00mm,1,10uF_16V,
C9,0805,1,470nF,
D1,D_SOD-123,1,3.3V,
"D2, D4",D_SMA,2,1N5819,
"D3, D5",LED_D3.0mm,2,Red,
D6,LED_D3.0mm,1,Green,
"D7, D8",D_SMA,2,1N5824,
J1,"TerminalBlock_Phoenix_PT-1,5-4-3.5-H_1x04_P3.50mm_Horizontal",1,PUMP,
J11,"TerminalBlock_Phoenix_PT-1,5-2-3.5-H_1x02_P3.50mm_Horizontal",1,INPUT,
J15,TestPoint_Keystone_5015_Micro_Mini,1,BSEN,
J2,PinHeader_1x03_P2.54mm_Vertical,1,SOIL SENSOR,
J3,PinHeader_1x03_P2.54mm_Vertical,1,AM2301A,
J4,PinSocket_1x04_P2.54mm_Vertical,1,OLED SCREEN,
J5,PinSocket_1x04_P2.54mm_Vertical,1,Ultra Sonic,
J7,PinHeader_1x04_P2.54mm_Vertical,1,USB_C Conn,
JP1,SolderJumper-2_P1.3mm_Open_Pad1.0x1.5mm,1,~,
"L1, L2",L_12x12mm_H6mm,2,33uH,
OC1,DIP-4_W7.62mm_SMDSocket_SmallPads,1,PC817XI,
"Q1, Q2",SOT-23_Handsoldering,2,IRLML6344,
Q3,SOT-363_SC-70-6,1,UMH3N,
"R1, R11, R14, R15, R2, R3, R4, R5, R9",0805,9,10k,
"R10, R12, R13",0805,3,330R,
R6,0805,1,20k,
R7,0805,1,1k,
R8,0805,1,2k,
SW1,PinHeader_1x06_P2.54mm_Vertical,1,RotaryEncoder,
SW2,SW_SPST_CK_KXT3,1,RESET,
SW3,SW_SPST_CK_KXT3,1,FLASH,
U1,SOT-223-3_TabPin2,1,AMS1117-3.3,
U2,ESP32-WROOM-32U,1,ESP32-WROOM,
"U3, U4",TO-263-5_TabPin6,2,LM2596S-3.3V,
U5,SOIC-16_3.9x9.9mm_P1.27mm,1,CH340C,
Y1,Crystal_HC49-4H_Vertical,1,12MHz,

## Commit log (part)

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2025-11-21 update from work
2025-11-24 done with schematic and block diagram
2025-11-25 done and ready for production
2025-11-25 Added Images
2025-11-25 Added more images
2025-12-09 update from home
2025-12-09 Updates from Work
2025-12-11 Project Initialization
2025-12-15 Block Diagram Uploaded
2025-12-19 reuploaded the block diagram
2025-12-20 Done with Schematic Diagram
2025-12-20 Schematic Reuploaded
2025-12-22 Done with schematic
2026-01-01 Done with the block diagram
2026-01-01 🚀 Initial KiCad structure setup
2026-01-01 Updated the block diagram
2026-01-02 Netlist class set
2026-01-04 Ready for Production
2026-01-06 Schematic in making
2026-01-06 sync updates
2026-01-06 Update on production
2026-01-07 done with block diagram
2026-01-10 Reference materials updated
2026-01-12 deleted some files to fix an issue with backup file
2026-01-17 Schematic diagram updated
2026-02-14 Created using Colab
